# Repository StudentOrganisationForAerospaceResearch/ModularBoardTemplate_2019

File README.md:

# SensorBoard_ModularTemplate_2019

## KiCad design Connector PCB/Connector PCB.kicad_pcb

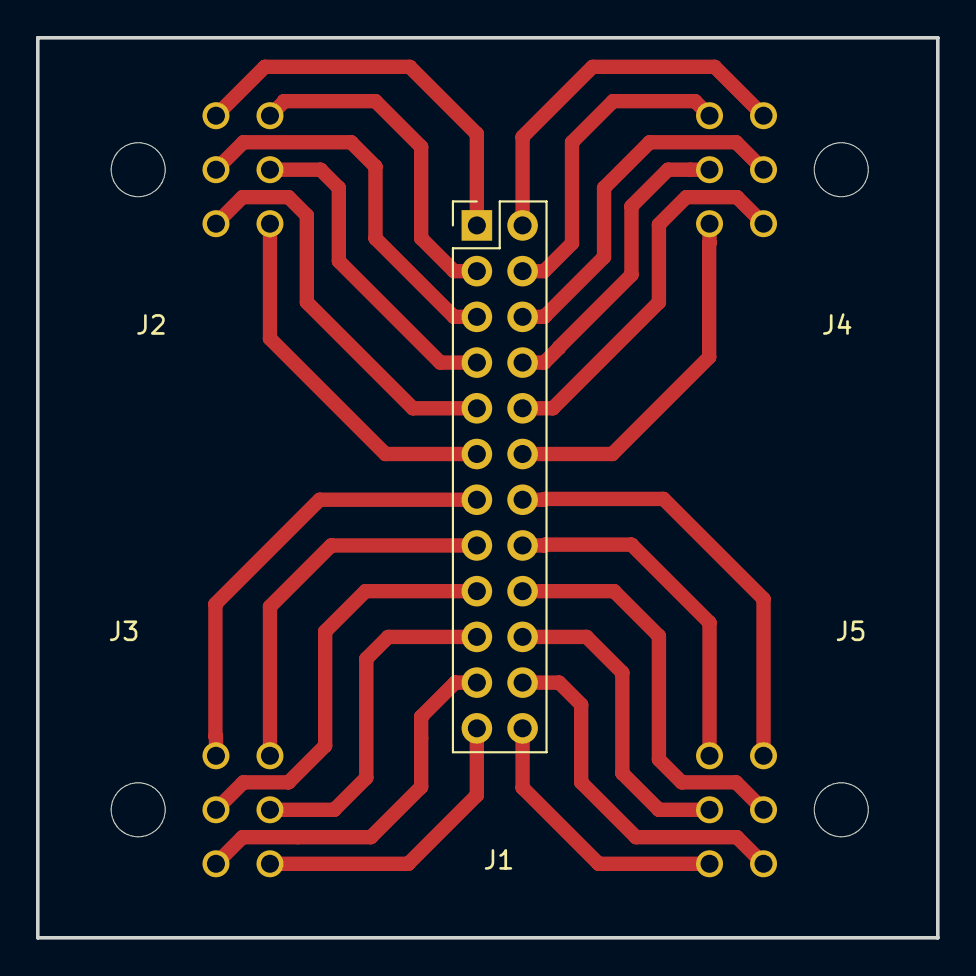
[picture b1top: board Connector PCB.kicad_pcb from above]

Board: 2 copper layers, 50.0 x 50.0 mm, 5 parts (0 on the bottom side), 24 nets.

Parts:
J1: 2x12 Pin Header; Pin_Header_Straight_2x12_Pitch2.54mm
J2, J3, J4, J5: 2x3 Molex; Molex_Micro-Fit_3.0_43045-0600_2x03_P3.00mm_Horizontal_flip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

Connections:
unnamed: J1.1, J2.1
unnamed: J1.2, J2.2
unnamed: J1.3, J2.3
unnamed: J1.4, J2.4
unnamed: J1.5, J2.5
unnamed: J1.6, J2.6
unnamed: J1.7, J3.1
unnamed: J1.8, J3.2
unnamed: J1.9, J3.3
unnamed: J1.10, J3.4
unnamed: J1.11, J3.5
unnamed: J1.12, J3.6
unnamed: J1.13, J4.1
unnamed: J1.14, J4.2
unnamed: J1.15, J4.3
unnamed: J1.16, J4.4
unnamed: J1.17, J4.5
unnamed: J1.18, J4.6
unnamed: J1.19, J5.1
unnamed: J1.20, J5.2
unnamed: J1.21, J5.3
unnamed: J1.22, J5.4
unnamed: J1.23, J5.5
unnamed: J1.24, J5.6

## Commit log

2019-01-21 Basic Git Terminology - TBF
2019-01-25 Initial commit for Exercise 1
2019-01-25 Created Instructions for Exercise 1
2019-01-25 Updated Ex1. Instructions
2019-01-25 Fixed typos
2019-01-28 I have completed Ex1.
2019-01-28 Added an extra instruction to prevent confusion
2019-01-28 Completed this exercise ting.
2019-02-01 Trying the exercise again to see if I remember
2019-02-01 Test
